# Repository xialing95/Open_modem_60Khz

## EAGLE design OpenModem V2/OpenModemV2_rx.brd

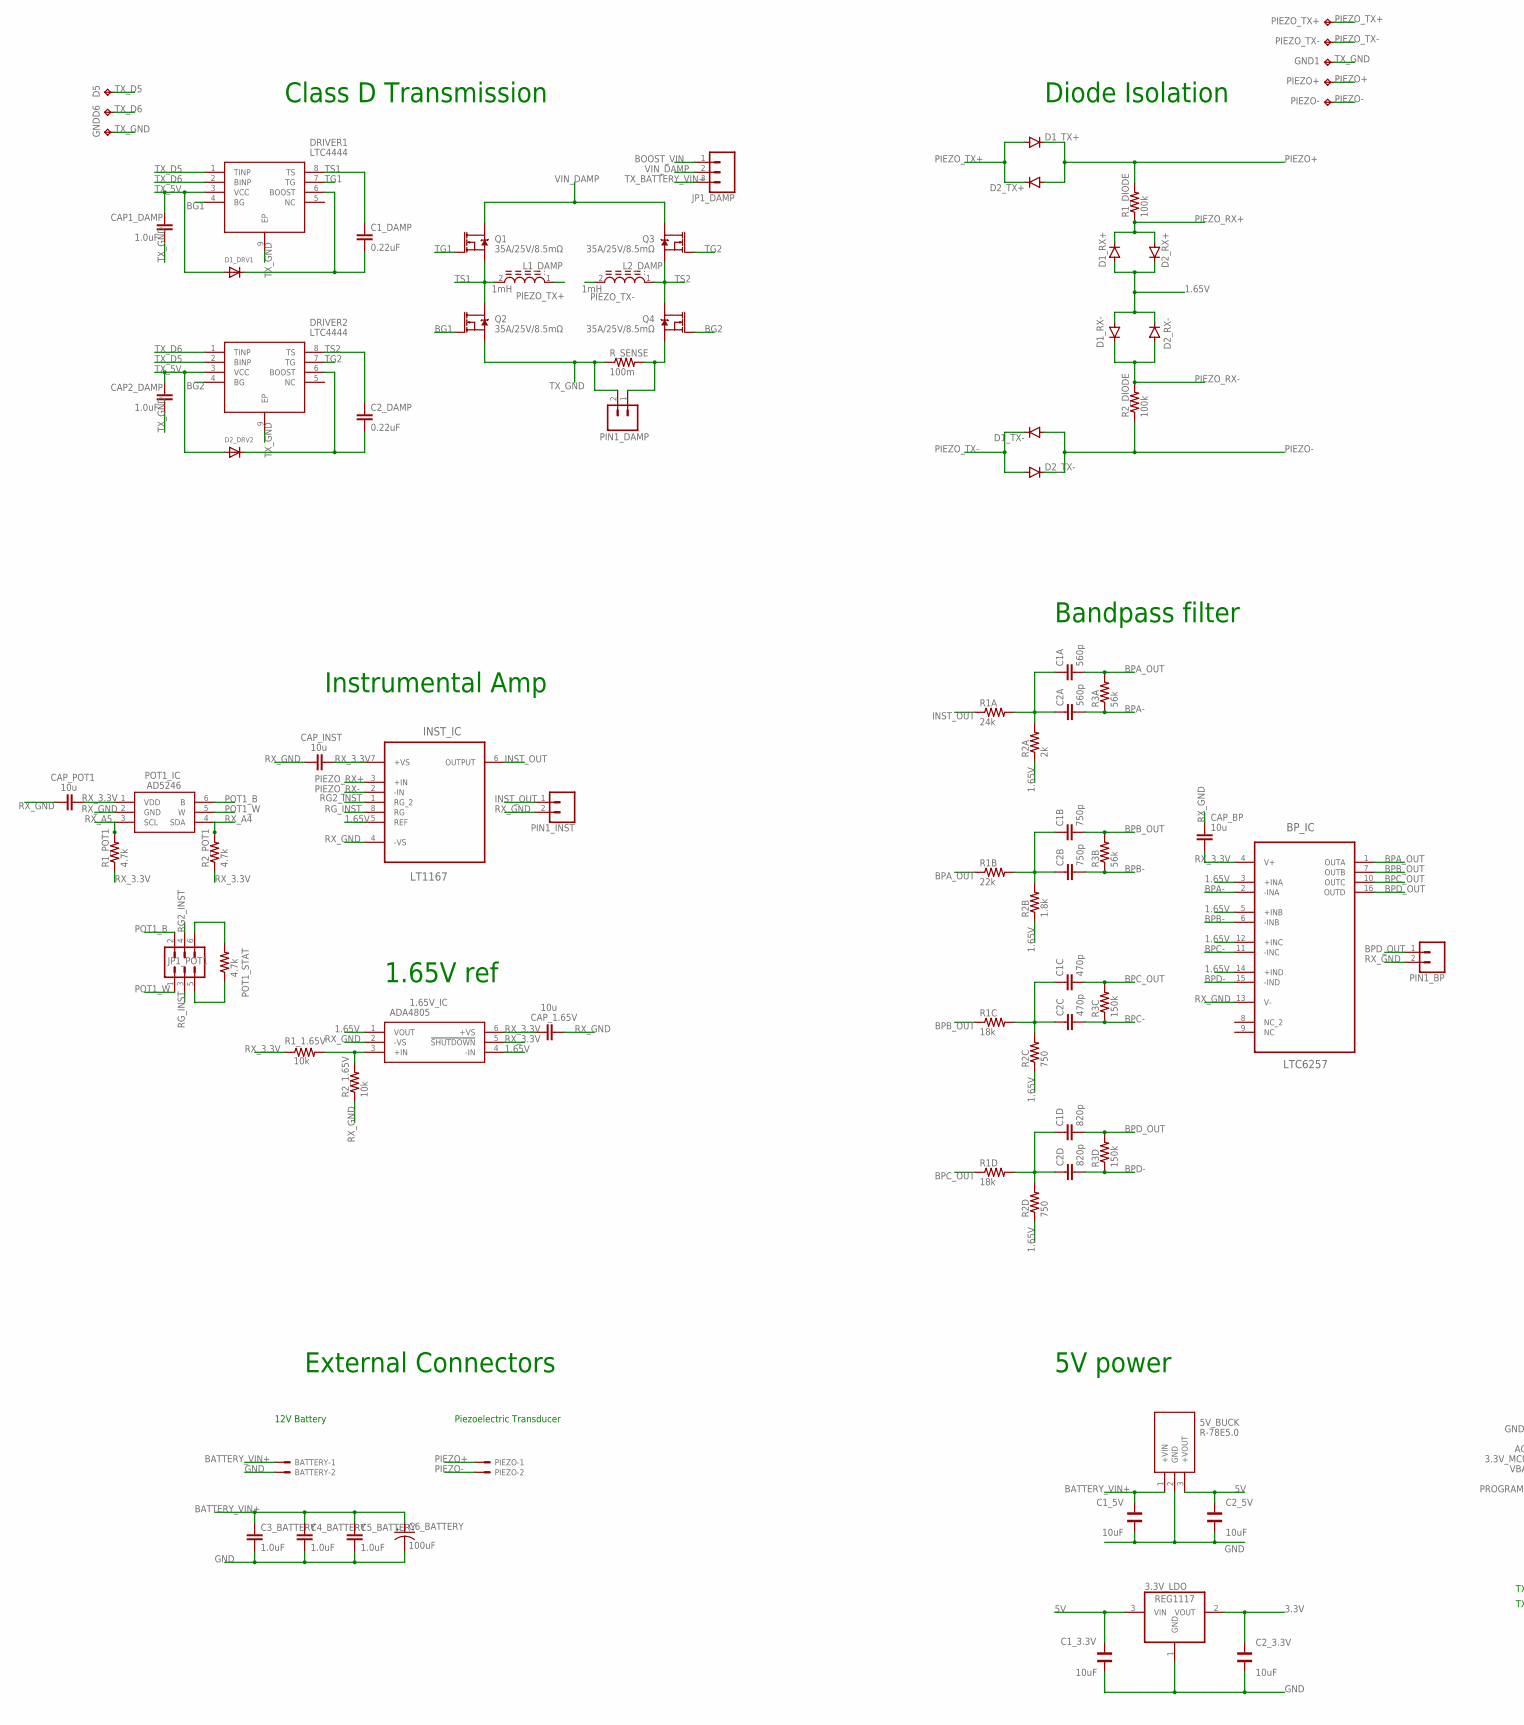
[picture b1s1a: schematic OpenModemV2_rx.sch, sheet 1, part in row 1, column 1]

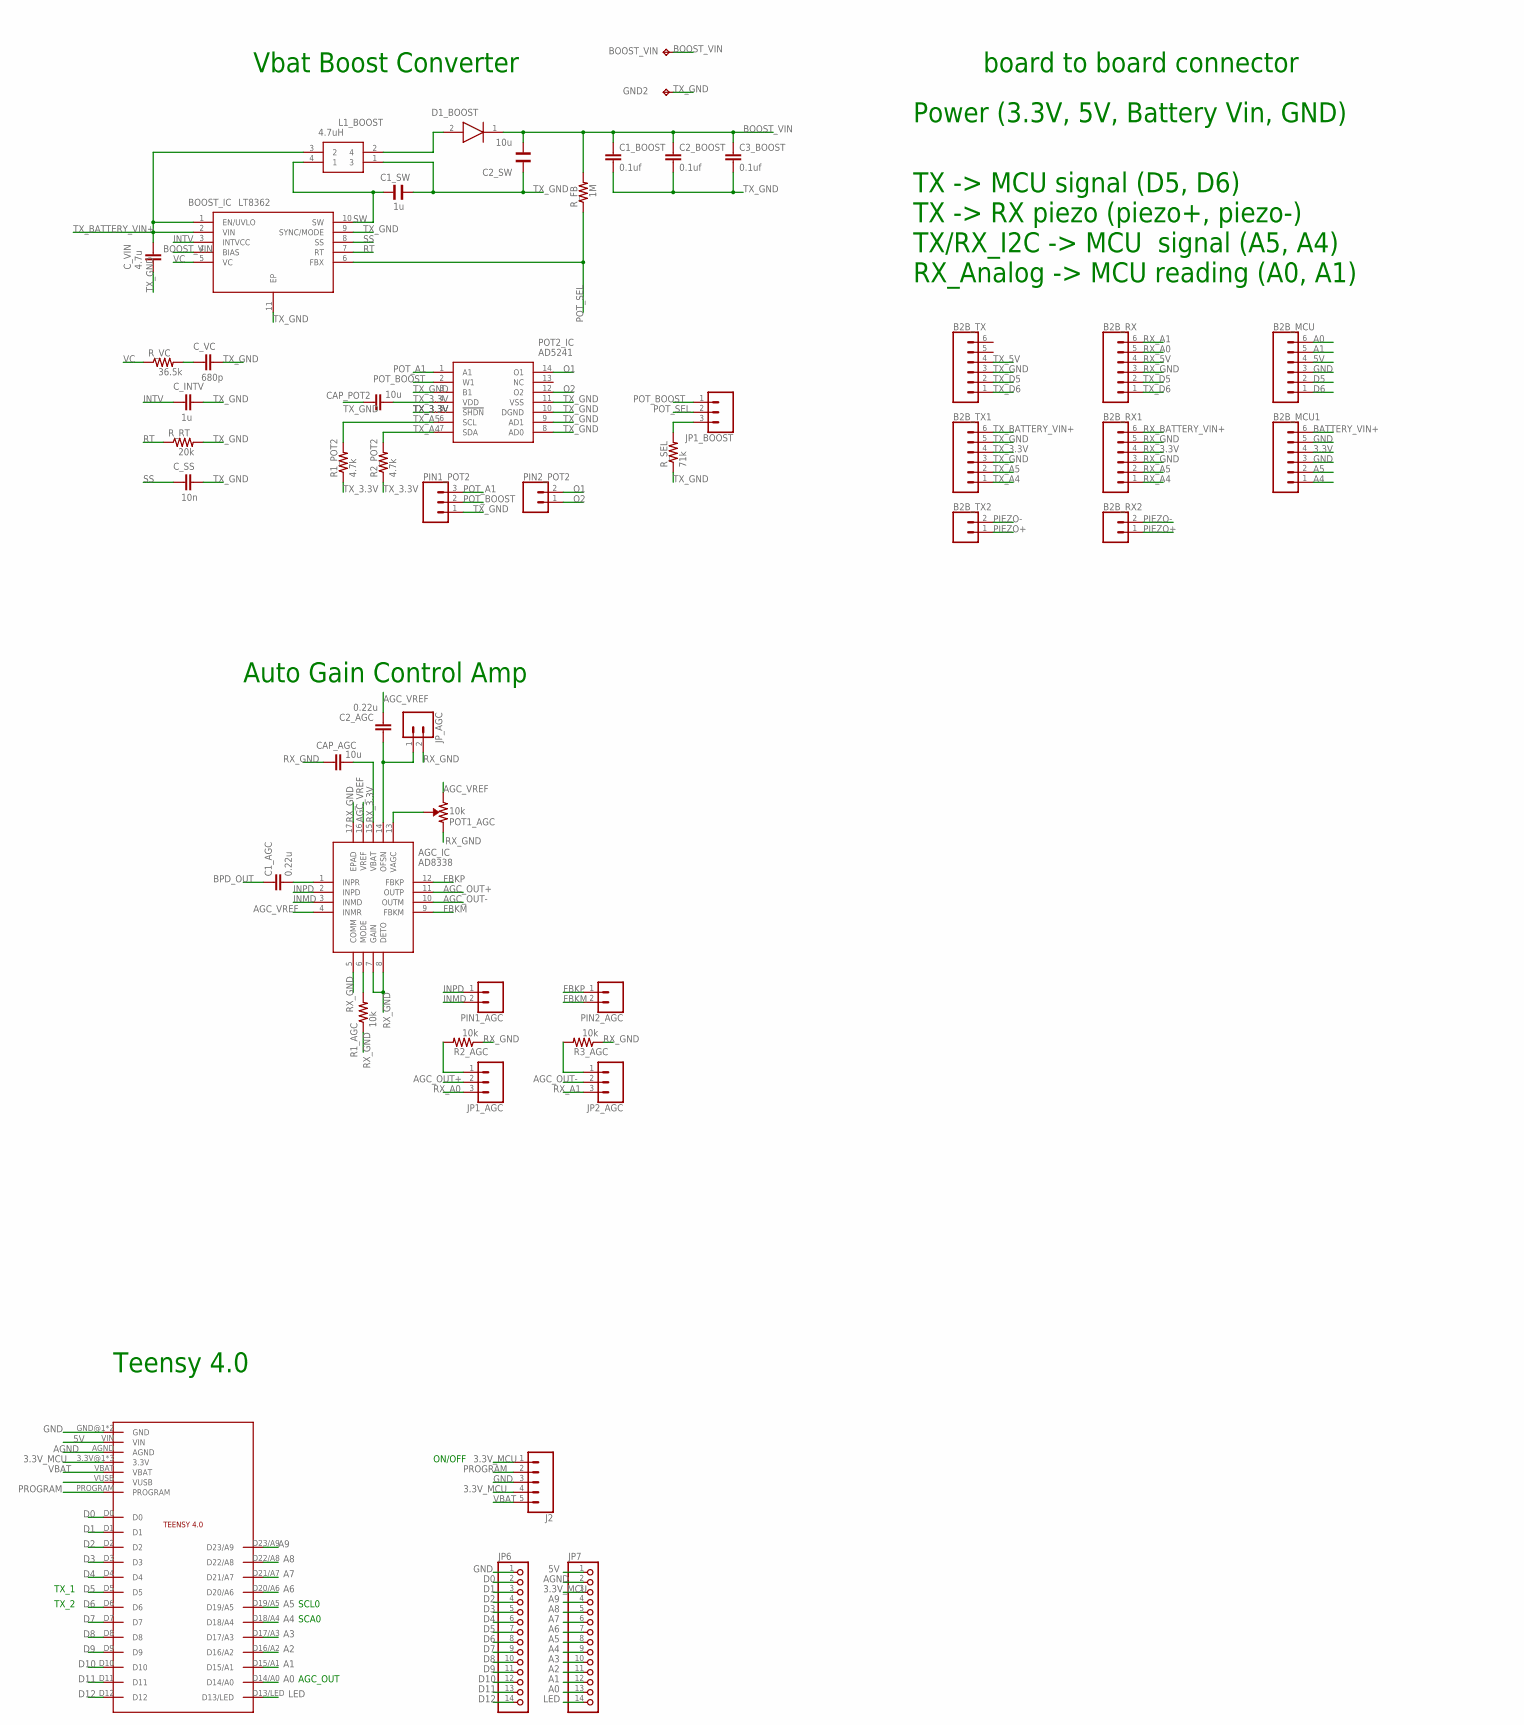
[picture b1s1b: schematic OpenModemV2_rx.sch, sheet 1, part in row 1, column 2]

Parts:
1.65V_IC: ADA4805; SOT95P280X145-6N
3.3V_LDO: REG1117; SOT223
5V_BUCK: R-78E5.0; R-78E5.0-1.0
AGC_IC: AD8338; QFN50P300X300X80-17N
B2B_MCU, B2B_MCU1, B2B_RX, B2B_RX1, B2B_TX, B2B_TX1: CONN_06SILK_FEMALE_PTH; 1X06
B2B_RX2, B2B_TX2: CONN_02; 1X02
BATTERY: 22-27-2021-02; 6410-02
BOOST_IC: LT8362; SON50P300X300X80-11N
BOOST_VIN: TPPAD1-13; P1-13
BP_IC: LTC6257; SOP50P490X110-16N
C1A, C2A: 560p; C0402
C1B, C2B: 750p; C0402
C1C, C2C: 470p; C0402
C1D, C2D: 820p; C0402
C1_3.3V, C1_5V, C2_3.3V, C2_5V: 10uF; WCAP-CSGP_0603_REFLOW
C1_AGC, C2_AGC: 0.22u; C0402
C1_BOOST, C2_BOOST, C3_BOOST: 0.1uf; 0805
C1_DAMP, C2_DAMP: 0.22uF; 0603
C1_SW: 1u; WCAP-CSGP_1206
C2_SW: 10u; WCAP-CSGP_1206
C3_BATTERY, C4_BATTERY, C5_BATTERY: 1.0uF; 0805
C6_BATTERY: 100uF; PANASONIC_D
CAP1_DAMP, CAP2_DAMP: 1.0uF; 0603
CAP_1.65V: 10u; C0402
CAP_AGC: 10u; C0402
CAP_BP: 10u; C0402
CAP_INST: 10u; C0402
CAP_POT1, CAP_POT2: 10u; C0402
C_INTV: 1u; C0402
C_SS: 10n; C0402
C_VC: 680p; C0402
C_VIN: 4.7u; C0402
D1_BOOST: DFLS260-7; POWERDI123
D1_DRV1, D2_DRV2: DIODESOD-323F; SOD-323F
D1_RX+, D1_RX-, D1_TX+, D1_TX-, D2_RX+, D2_RX-, D2_TX+, D2_TX-: DIODE-SOD523; SOD523
D5, D6: TPPAD1-13; P1-13
DRIVER1, DRIVER2: LTC4444; SOP65P490X110-9N
GND, GND1, GND2: TPPAD1-13; P1-13
INST_IC: LT1167; SOIC127P600X175-8N
J2: CONN_05; 1X05
JP1_AGC, JP1_BOOST, JP1_DAMP, JP2_AGC: CONN_03; 1X03
JP1_POT1: CONN_03X2NO_SILK; 2X3-NS
JP6, JP7: PINHD-1X14-CB; 1X14-CB
JP_AGC: CONN_02; 1X02
L1_BOOST: 4.7uH; WE-DD_7332/734512
L1_DAMP, L2_DAMP: 1mH; INDP125125X600N
PIEZO: 22-27-2021-02; 6410-02
PIEZO+: TPPAD1-13; P1-13
PIEZO-: TPPAD1-13; P1-13
PIEZO_TX+: TPPAD1-13; P1-13
PIEZO_TX-: TPPAD1-13; P1-13
PIN1_AGC, PIN1_BP, PIN1_DAMP, PIN1_INST, PIN2_AGC, PIN2_POT2: CONN_02; 1X02
PIN1_POT2: CONN_03; 1X03
POT1_AGC: 10k; TRIMPOT-SMD-3MM-CLOSED
POT1_IC: AD5246; SOT65P210X110-6N
POT1_STAT: 4.7k; R0603
POT2_IC: AD5241; SOP65P640X120-14N
Q1, Q2, Q3, Q4: 35A/25V/8.5mΩ; DPAK
R1A: 24k; R0603
R1B: 22k; R0603
R1C, R1D: 18k; R0603
R1_1.65V, R1_AGC, R2_1.65V, R2_AGC, R3_AGC: 10k; R0603
R1_DIODE, R2_DIODE: 100k; R0603
R1_POT1, R1_POT2, R2_POT1, R2_POT2: 4.7k; R0603
R2A: 2k; R0603
R2B: 1.8k; R0603
R2C, R2D: 750; R0603
R3A, R3B: 56k; R0603
R3C, R3D: 150k; R0603
R_FB: 1M; R0603
R_RT: 20k; R0603
R_SEL: 71k; R0603
R_SENSE: 100m; M1206
R_VC: 36.5k; R0603
U$1: TEENSY4.0

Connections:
1.65V: 1.65V_IC.1 (VOUT), 1.65V_IC.4 (-IN), BP_IC.3 (+INA), BP_IC.5 (+INB), BP_IC.12 (+INC), BP_IC.14 (+IND), D1_RX+.A, D1_RX-.A, D2_RX+.C, D2_RX-.C, INST_IC.5 (REF), R2A.1, R2B.1, R2C.1, R2D.1
3.3V: 3.3V_LDO.2 (VOUT), B2B_MCU1.4, C2_3.3V.2
3.3V_MCU: J2.1, J2.4, JP7.3, U$1.3.3V@1 (3.3V), U$1.3.3V@2 (3.3V), U$1.ON/OFF (3.3V)
5V: 3.3V_LDO.3 (VIN), 5V_BUCK.3 (+VOUT), B2B_MCU.4, C1_3.3V.2, C2_5V.2, JP7.1, U$1.VIN
A0: B2B_MCU.6, JP7.13, U$1.D14/A0
A1: B2B_MCU.5, JP7.12, U$1.D15/A1
A2: JP7.11, U$1.D16/A2
A3: JP7.10, U$1.D17/A3
A4: B2B_MCU1.1, JP7.9, U$1.D18/A4
A5: B2B_MCU1.2, JP7.8, U$1.D19/A5
A6: JP7.7, U$1.D20/A6
A7: JP7.6, U$1.D21/A7
A8: JP7.5, U$1.D22/A8
A9: JP7.4, U$1.D23/A9
AGC_OUT+: AGC_IC.11 (OUTP), JP1_AGC.2
AGC_OUT-: AGC_IC.10 (OUTM), JP2_AGC.2
AGC_VREF: AGC_IC.4 (INMR), AGC_IC.16 (VREF), C2_AGC.2, POT1_AGC.3 (CW)
AGND: JP7.2, U$1.AGND
BATTERY_VIN+: 5V_BUCK.1 (+VIN), B2B_MCU1.6, BATTERY.1, C1_5V.1, C3_BATTERY.1, C4_BATTERY.1, C5_BATTERY.1, C6_BATTERY.+
BG1: DRIVER1.4 (BG), Q2.1 (G)
BG2: DRIVER2.4 (BG), Q4.1 (G)
BOOST_VIN: BOOST_IC.4 (BIAS), BOOST_VIN.TP, C1_BOOST.1, C2_BOOST.1, C2_SW.1, C3_BOOST.1, D1_BOOST.1 (K), JP1_DAMP.1, R_FB.2
BPA-: BP_IC.2 (-INA), C2A.2, R3A.1
BPA_OUT: BP_IC.1 (OUTA), C1A.2, R1B.1, R3A.2
BPB-: BP_IC.6 (-INB), C2B.2, R3B.1
BPB_OUT: BP_IC.7 (OUTB), C1B.2, R1C.1, R3B.2
BPC-: BP_IC.11 (-INC), C2C.2, R3C.1
BPC_OUT: BP_IC.10 (OUTC), C1C.2, R1D.1, R3C.2
BPD-: BP_IC.15 (-IND), C2D.2, R3D.1
BPD_OUT: BP_IC.16 (OUTD), C1D.2, C1_AGC.1, PIN1_BP.1, R3D.2
D0: JP6.2, U$1.D0
D1: JP6.3, U$1.D1
D2: JP6.4, U$1.D2
D3: JP6.5, U$1.D3
D4: JP6.6, U$1.D4
D5: B2B_MCU.2, JP6.7, U$1.D5
D6: B2B_MCU.1, JP6.8, U$1.D6
D7: JP6.9, U$1.D7
D8: JP6.10, U$1.D8
D9: JP6.11, U$1.D9
D10: JP6.12, U$1.D10
D11: JP6.13, U$1.D11
D12: JP6.14, U$1.D12
FBKM: AGC_IC.9 (FBKM), PIN2_AGC.2
FBKP: AGC_IC.12 (FBKP), PIN2_AGC.1
GND: 3.3V_LDO.1 (GND), 5V_BUCK.2 (GND), B2B_MCU.3, B2B_MCU1.3, B2B_MCU1.5, BATTERY.2, C1_3.3V.1, C1_5V.2, C2_3.3V.1, C2_5V.1, C3_BATTERY.2, C4_BATTERY.2, C5_BATTERY.2, C6_BATTERY.-, J2.3, JP6.1, U$1.GND@1 (GND), U$1.GND@2 (GND)
INMD: AGC_IC.3 (INMD), PIN1_AGC.2
INPD: AGC_IC.2 (INPD), PIN1_AGC.1
INST_OUT: INST_IC.6 (OUTPUT), PIN1_INST.1, R1A.1
INTV: BOOST_IC.3 (INTVCC), C_INTV.2
LED: JP7.14, U$1.D13/LED
unnamed: C1_DAMP.2, D1_DRV1.C, DRIVER1.6 (BOOST)
unnamed: C2_DAMP.2, D2_DRV2.C, DRIVER2.6 (BOOST)
unnamed: JP1_POT1.6, POT1_STAT.2
unnamed: C1A.1, C2A.1, R1A.2, R2A.2
unnamed: C1B.1, C2B.1, R1B.2, R2B.2
unnamed: C1C.1, C2C.1, R1C.2, R2C.2
unnamed: C1D.1, C2D.1, R1D.2, R2D.2
unnamed: C_VC.2, R_VC.2
unnamed: AGC_IC.6 (MODE), R1_AGC.2
unnamed: 1.65V_IC.3 (+IN), R1_1.65V.2, R2_1.65V.2
unnamed: AGC_IC.1 (INPR), C1_AGC.2
unnamed: JP1_POT1.5, POT1_STAT.1
unnamed: JP1_AGC.1, R2_AGC.2
unnamed: JP2_AGC.1, R3_AGC.2
unnamed: AGC_IC.14 (OFSN), C2_AGC.1, JP_AGC.1
unnamed: AGC_IC.13 (VAGC), POT1_AGC.2 (WIPER)
unnamed: PIN1_DAMP.1, Q4.3 (S), R_SENSE.2
unnamed: D1_BOOST.2 (A), L1_BOOST.2 (4)
unnamed: JP1_BOOST.3, R_SEL.2
O1: PIN2_POT2.2, POT2_IC.14 (O1)
O2: PIN2_POT2.1, POT2_IC.12 (O2)
PIEZO+: B2B_RX2.1, B2B_TX2.1, D1_TX+.C, D2_TX+.A, PIEZO.1, PIEZO+.TP, R1_DIODE.2
PIEZO-: B2B_RX2.2, B2B_TX2.2, D1_TX-.A, D2_TX-.C, PIEZO.2, PIEZO-.TP, R2_DIODE.1
PIEZO_RX+: D1_RX+.C, D2_RX+.A, INST_IC.3 (+IN), R1_DIODE.1
PIEZO_RX-: D1_RX-.C, D2_RX-.A, INST_IC.2 (-IN), R2_DIODE.2
PIEZO_TX+: D1_TX+.A, D2_TX+.C, L1_DAMP.1, PIEZO_TX+.TP
PIEZO_TX-: D1_TX-.C, D2_TX-.A, L2_DAMP.2, PIEZO_TX-.TP
POT1_B: JP1_POT1.2, POT1_IC.6 (B)
POT1_W: JP1_POT1.1, POT1_IC.5 (W)
POT_A1: PIN1_POT2.3, POT2_IC.1 (A1)
POT_BOOST: JP1_BOOST.1, PIN1_POT2.2, POT2_IC.2 (W1)
POT_SEL: BOOST_IC.6 (FBX), JP1_BOOST.2, R_FB.1
PROGRAM: J2.2, U$1.PROGRAM
RG2_INST: INST_IC.1 (RG_2), JP1_POT1.4
RG_INST: INST_IC.8 (RG), JP1_POT1.3
RT: BOOST_IC.7 (RT), R_RT.1
RX_3.3V: 1.65V_IC.5 (!SHUTDOWN), 1.65V_IC.6 (+VS), AGC_IC.15 (VBAT), B2B_RX1.4, BP_IC.4 (V+), CAP_1.65V.2, CAP_AGC.1, CAP_BP.1, CAP_INST.2, CAP_POT1.2, INST_IC.7 (+VS), POT1_IC.1 (VDD), R1_1.65V.1, R1_POT1.1, R2_POT1.1
RX_5V: B2B_RX.4
RX_A0: B2B_RX.5, JP1_AGC.3
RX_A1: B2B_RX.6, JP2_AGC.3
RX_A4: B2B_RX1.1, POT1_IC.4 (SDA), R2_POT1.2
RX_A5: B2B_RX1.2, POT1_IC.3 (SCL), R1_POT1.2
RX_BATTERY_VIN+: B2B_RX1.6
RX_GND: 1.65V_IC.2 (-VS), AGC_IC.5 (COMM), AGC_IC.7 (GAIN), AGC_IC.8 (DETO), AGC_IC.17 (EPAD), B2B_RX.3, B2B_RX1.3, B2B_RX1.5, BP_IC.13 (V-), CAP_1.65V.1, CAP_AGC.2, CAP_BP.2, CAP_INST.1, CAP_POT1.1, INST_IC.4 (-VS), JP_AGC.2, PIN1_BP.2, PIN1_INST.2, POT1_AGC.1 (CCW), POT1_IC.2 (GND), R1_AGC.1, R2_1.65V.1, R2_AGC.1, R3_AGC.1
SS: BOOST_IC.8 (SS), C_SS.2
SW: BOOST_IC.10 (SW), C1_SW.2, L1_BOOST.4 (1)
TG1: DRIVER1.7 (TG), Q1.1 (G)
TG2: DRIVER2.7 (TG), Q3.1 (G)
TS1: C1_DAMP.1, DRIVER1.8 (TS), L1_DAMP.2, Q1.3 (S), Q2.4 (D)
TS2: C2_DAMP.1, DRIVER2.8 (TS), L2_DAMP.1, Q3.3 (S), Q4.4 (D)
TX_3.3V: B2B_TX1.4, CAP_POT2.1, POT2_IC.4 (VDD), POT2_IC.5 (!SHDN), R1_POT2.1, R2_POT2.1
TX_5V: B2B_TX.4, CAP1_DAMP.1, CAP2_DAMP.1, D1_DRV1.A, D2_DRV2.A, DRIVER1.3 (VCC), DRIVER2.3 (VCC)
TX_A4: B2B_TX1.1, POT2_IC.7 (SDA), R2_POT2.2
TX_A5: B2B_TX1.2, POT2_IC.6 (SCL), R1_POT2.2
TX_BATTERY_VIN+: B2B_TX1.6, BOOST_IC.1 (EN/UVLO), BOOST_IC.2 (VIN), C_VIN.2, JP1_DAMP.3, L1_BOOST.3 (2)
TX_D5: B2B_RX.2, B2B_TX.2, D5.TP, DRIVER1.1 (TINP), DRIVER2.2 (BINP)
TX_D6: B2B_RX.1, B2B_TX.1, D6.TP, DRIVER1.2 (BINP), DRIVER2.1 (TINP)
TX_GND: B2B_TX.3, B2B_TX1.3, B2B_TX1.5, BOOST_IC.9 (SYNC/MODE), BOOST_IC.11 (EP), C1_BOOST.2, C1_SW.1, C2_BOOST.2, C2_SW.2, C3_BOOST.2, CAP1_DAMP.2, CAP2_DAMP.2, CAP_POT2.2, C_INTV.1, C_SS.1, C_VC.1, C_VIN.1, DRIVER1.9 (EP), DRIVER2.9 (EP), GND.TP, GND1.TP, GND2.TP, L1_BOOST.1 (3), PIN1_DAMP.2, PIN1_POT2.1, POT2_IC.3 (B1), POT2_IC.8 (AD0), POT2_IC.9 (AD1), POT2_IC.10 (DGND), POT2_IC.11 (VSS), Q2.3 (S), R_RT.2, R_SEL.1, R_SENSE.1
VBAT: J2.5, U$1.VBAT
VC: BOOST_IC.5 (VC), R_VC.1
VIN_DAMP: JP1_DAMP.2, Q1.4 (D), Q3.4 (D)

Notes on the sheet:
Class D Transmission
Instrumental Amp
Bandpass filter
Auto Gain Control Amp
Teensy 4.0
5V power
Diode Isolation
1.65V ref
Vbat Boost Converter
SCL0
SCA0
TX_1
TX_2
AGC_OUT
External Connectors
12V Battery
Piezoelectric Transducer
board to board connector
Power (3.3V, 5V, Battery Vin, GND)
TX -> MCU signal (D5, D6) TX -> RX piezo (piezo+, piezo-) TX/RX_I2C -> MCU signal (A5, A4) RX_Analog -> MCU reading (A0, A1)
ON/OFF

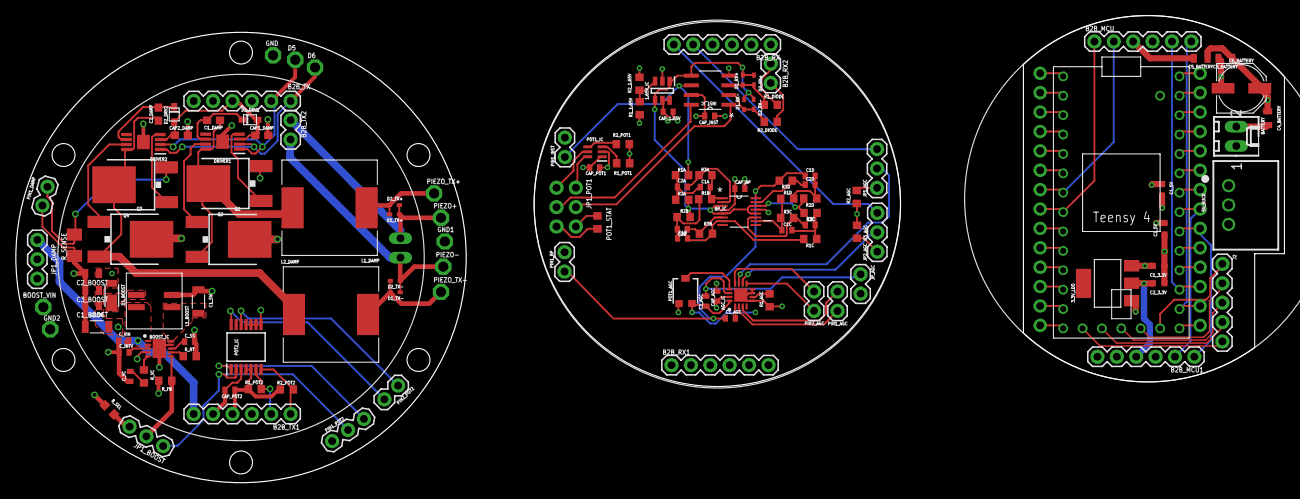
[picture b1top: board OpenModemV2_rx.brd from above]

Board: 4 copper layers, 166.2 x 61.2 mm, 133 parts (1 on the bottom side), 110 nets.

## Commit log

2023-05-25 Add files via upload
    Initial Commit

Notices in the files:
parts and their libraries:
Wurth_Elektronik_Passive_Capacitors_rev1: Copyright: Würth Elektronik
SparkFun-Capacitors: Licensing: Creative Commons ShareAlike 4.0 International - https://creativecommons.org/licenses/by-sa/4.0
